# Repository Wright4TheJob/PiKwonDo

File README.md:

# PiKwonDo
A Raspberry Pi-based system for scoring TaeKwonDo sparring matches.

# Goals
The goal of this project is to create an inexpensive system for scoring TaeKwonDo sparring. This system is intended to be small and easily modified to suit the needs of individual Dojangs. The system is currently designed for electronic scoring manually triggered by corner judges.

Phase 1 of the judging system will use judge triggers connected by wires to the central controller. Phase 2 is intended to use wireless judge trigger systems or mobile phone connectivity.

While the system is designed to mimic expensive World TaeKwonDo-approved systems, it is not certified for official tournament use.

# Status
The project is under alpha development. Software has been developed but has yet to be tested with the hardware. Electronics are designed for single-sided PCB routing and have all completed initial design but have not been tested yet. Cases are designed for 3D printing. Hardware and software folders have individual README files with more particular statuses and todo items.

All design files and software are provided "as-is." Any stable releases will be bundled for easy download, but this does not guarantee suitability for your particular setup.

Bill of Materials (BOM) table validation: 

# Software
The judging software and UI is written in python and QT. A dedicated thread scans the status of judge controller buttons. Game logic and UI are run as the primary thread.
<!--Wireless versions of the software may use Twisted to create a local server.-->

# Electronics
Controllers use shift registers to store and sequentially read out the values of the buttons in each controller. Judge controllers have 10 buttons and the timer controller has 5. PCBs are designed for single-side milling, with traces no smaller than 0.4mm and trace gaps of 0.3mm. Through-hole components are used for hand soldering and occasional jumper wires are used.

# Hardware
The system is designed and tested on a Raspberry Pi 3B+. Physical wiring uses phone jacks and standard 4-conductor phone cables for data communication to judging triggers. Cases are designed for 3D printing and modeled in Solidworks.
<!--Future iterations may investigate the viability of using the Raspberry Pi Zero W.-->

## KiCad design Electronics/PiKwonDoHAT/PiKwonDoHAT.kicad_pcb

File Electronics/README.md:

# Electronics
The PiKwonDo is made of four different electrical boards bundled into three unique and connected elements: the processing core, the PiKwonDoHAT, the timer control board, and the judge control board.

All circuits and PCBs are modeled in KiCAD. PCBs are minimal complexity necessary. Boards are intended to be single-sided and capable of being milled on a home circuit board router.

# Processing Core
The core processing unit of the PiKwonDo is a Raspberry Pi. The system is being tested on a Raspberry Pi 3B+.

# PiKwonDoHAT
The PiKwonDoHAT board mounts to the Raspberry Pi and provides the GPIO interface to the RJ12 ports and external boxes. This board contains no logic, simply provides an I/O adapter.

# Peripheral Boxes
All the peripheral boxes (timer and judge boxes), use shift registers to store the button states and sequentially report buttons states to the processor when requested. This method reduces the number of data lines to the central processor and de-couples the number of data lines from the number of buttons per peripheral.

An LED is lighted by the shift pin of the shift register and will illuminate whenever the central processor is querying the state of the buttons.

## Timer
The timer control board contains 5 buttons: three to control the round timing (Start, Pause, Reset), and two penalty buttons (Red and Blue). A single shift register is used to output the state of these 5 buttons.

## Judge
The judge box board contains 10 buttons corresponding to point values of 1 through 5 for both red and blue. Two shift registers passing data in series are used to store the values of all 10 buttons.

# Status
Circuit diagrams have been completed and initial PCB layout and trace routing is done.

## TODO
* Finalize button positions on timer controller.
* Finalize BOM and component selection.
* Update component footprints to reflect BOM.
* Update trace size and spacing to ensure manufacturability.

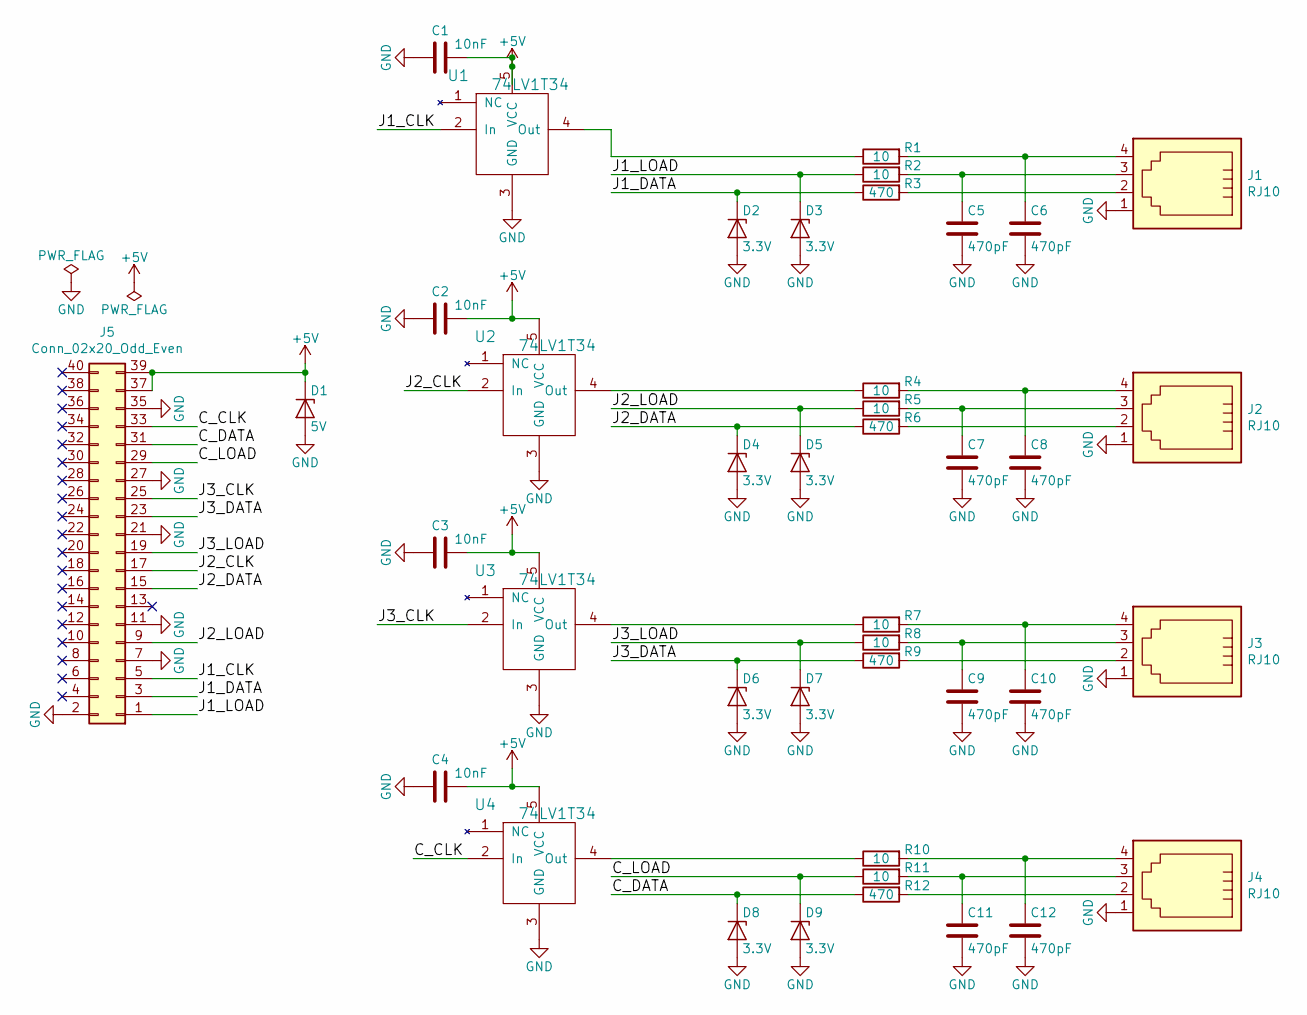
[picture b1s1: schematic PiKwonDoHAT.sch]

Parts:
C1, C2, C3, C4: 10nF; C_1206_3216Metric_Pad1.42x1.75mm_HandSolder
C5, C6, C7, C8, C9, C10, C11, C12: 470pF; C_1206_3216Metric_Pad1.42x1.75mm_HandSolder
D1: 5V; D_SOD-123
D2, D3, D4, D5, D6, D7, D8, D9: 3.3V; D_SOD-123
J1, J2, J3, J4: RJ10; RJ14
J5: Conn_02x20_Odd_Even; PinSocket_2x20_P2.54mm_Vertical
R1, R2, R4, R5, R7, R8, R10, R11: 10; R_1206_HandSoldering
R3, R6, R9, R12: 470; R_1206_HandSoldering
U1, U2, U3, U4: 74LV1T34; SOT-23-5_HandSoldering

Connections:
+5V: C1.1, C2.1, C3.1, C4.1, D1.1 (K), J5.37, J5.39, U1.5 (VCC), U2.5 (VCC), U3.5 (VCC), U4.5 (VCC)
/C_CLK: J5.33, U4.2 (In)
/C_DATA: D8.1 (K), J5.31, R12.1
/C_LOAD: D9.1 (K), J5.29, R11.1
/J1_CLK: J5.5, U1.2 (In)
/J1_DATA: D2.1 (K), J5.3, R3.1
/J1_LOAD: D3.1 (K), J5.1, R2.1
/J2_CLK: J5.17, U2.2 (In)
/J2_DATA: D4.1 (K), J5.15, R6.1
/J2_LOAD: D5.1 (K), J5.9, R5.1
/J3_CLK: J5.25, U3.2 (In)
/J3_DATA: D6.1 (K), J5.23, R9.1
/J3_LOAD: D7.1 (K), J5.19, R8.1
GND: C1.2, C2.2, C3.2, C4.2, C5.2, C6.2, C7.2, C8.2, C9.2, C10.2, C11.2, C12.2, D1.2 (A), D2.2 (A), D3.2 (A), D4.2 (A), D5.2 (A), D6.2 (A), D7.2 (A), D8.2 (A), D9.2 (A), J1.1, J2.1, J3.1, J4.1, J5.2, J5.7, J5.11, J5.21, J5.27, J5.35, U1.3 (GND), U2.3 (GND), U3.3 (GND), U4.3 (GND)
unnamed: C5.1, J1.3, R2.2
unnamed: C6.1, J1.4, R1.2
unnamed: C7.1, J2.3, R5.2
unnamed: C8.1, J2.4, R4.2
unnamed: C9.1, J3.3, R8.2
unnamed: C10.1, J3.4, R7.2
unnamed: C11.1, J4.3, R11.2
unnamed: C12.1, J4.4, R10.2
unnamed: J1.2, R3.2
unnamed: J2.2, R6.2
unnamed: J3.2, R9.2
unnamed: J4.2, R12.2
unnamed: R1.1, U1.4 (Out)
unnamed: R4.1, U2.4 (Out)
unnamed: R7.1, U3.4 (Out)
unnamed: R10.1, U4.4 (Out)

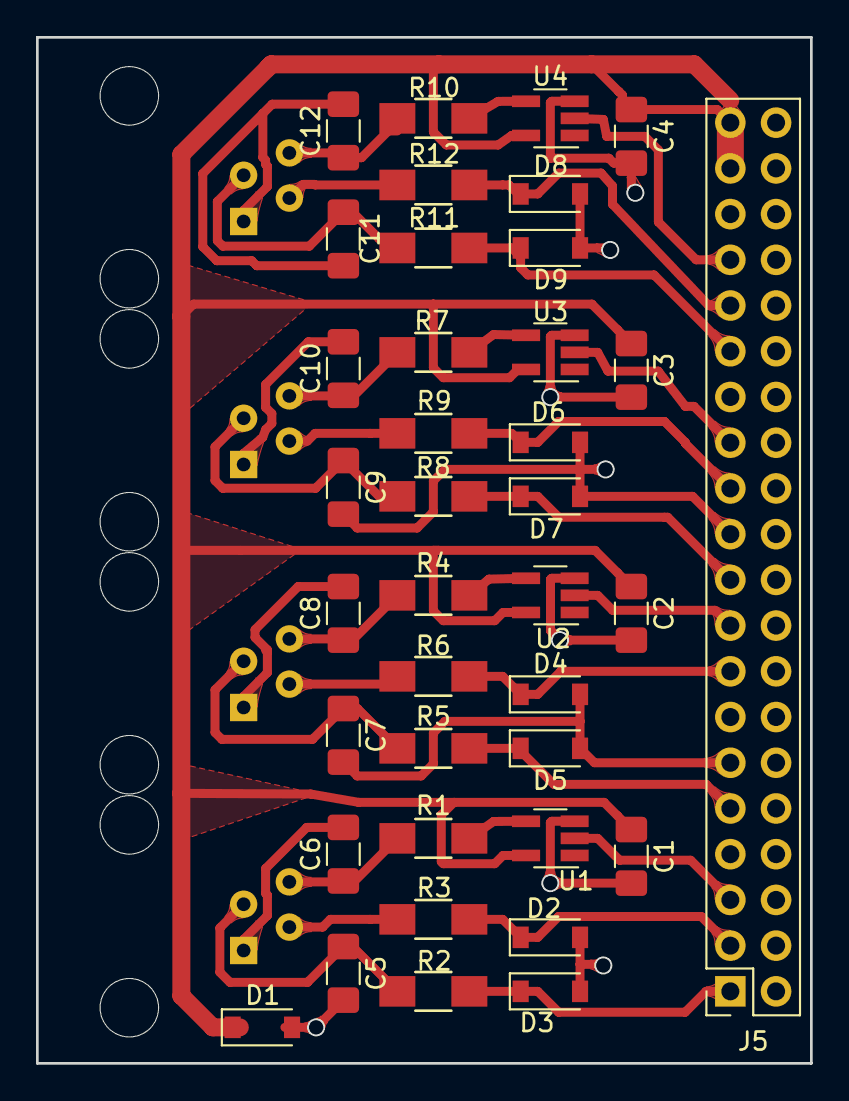
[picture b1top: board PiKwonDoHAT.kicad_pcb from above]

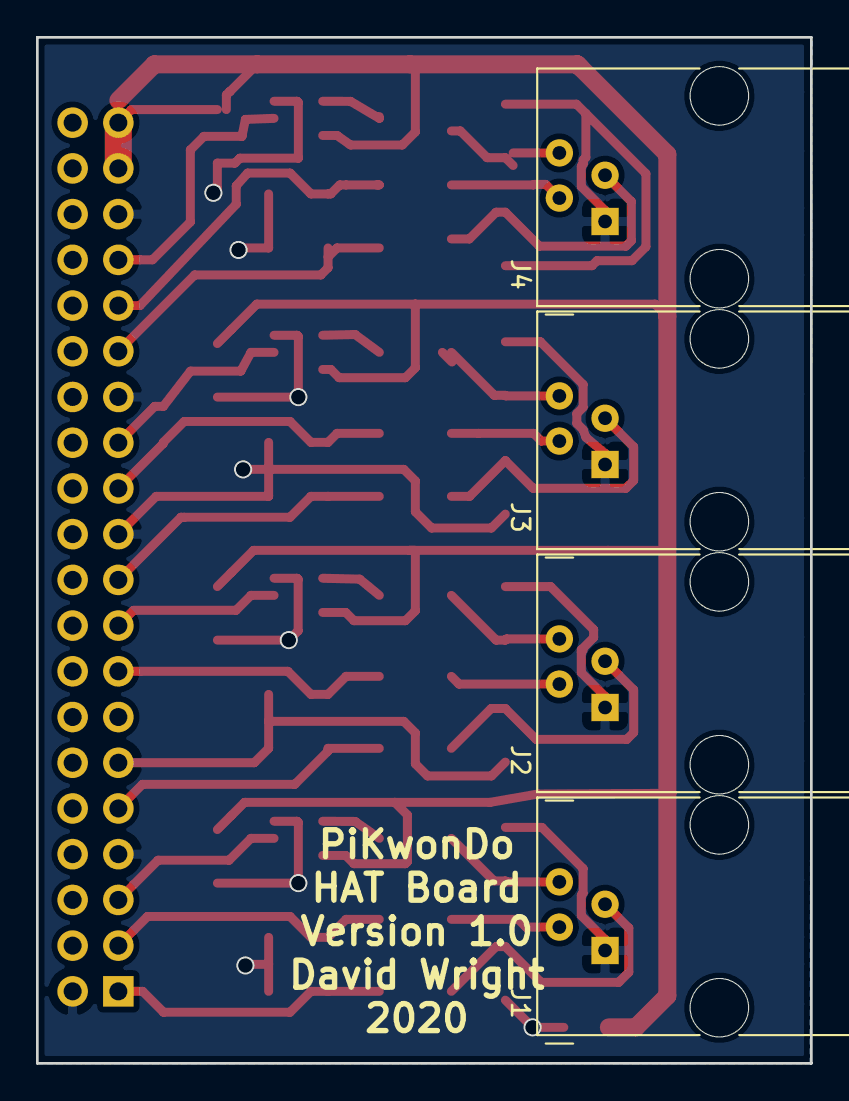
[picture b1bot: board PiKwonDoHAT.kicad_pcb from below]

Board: 2 copper layers, 43.0 x 57.0 mm, 42 parts (4 on the bottom side), 30 nets.

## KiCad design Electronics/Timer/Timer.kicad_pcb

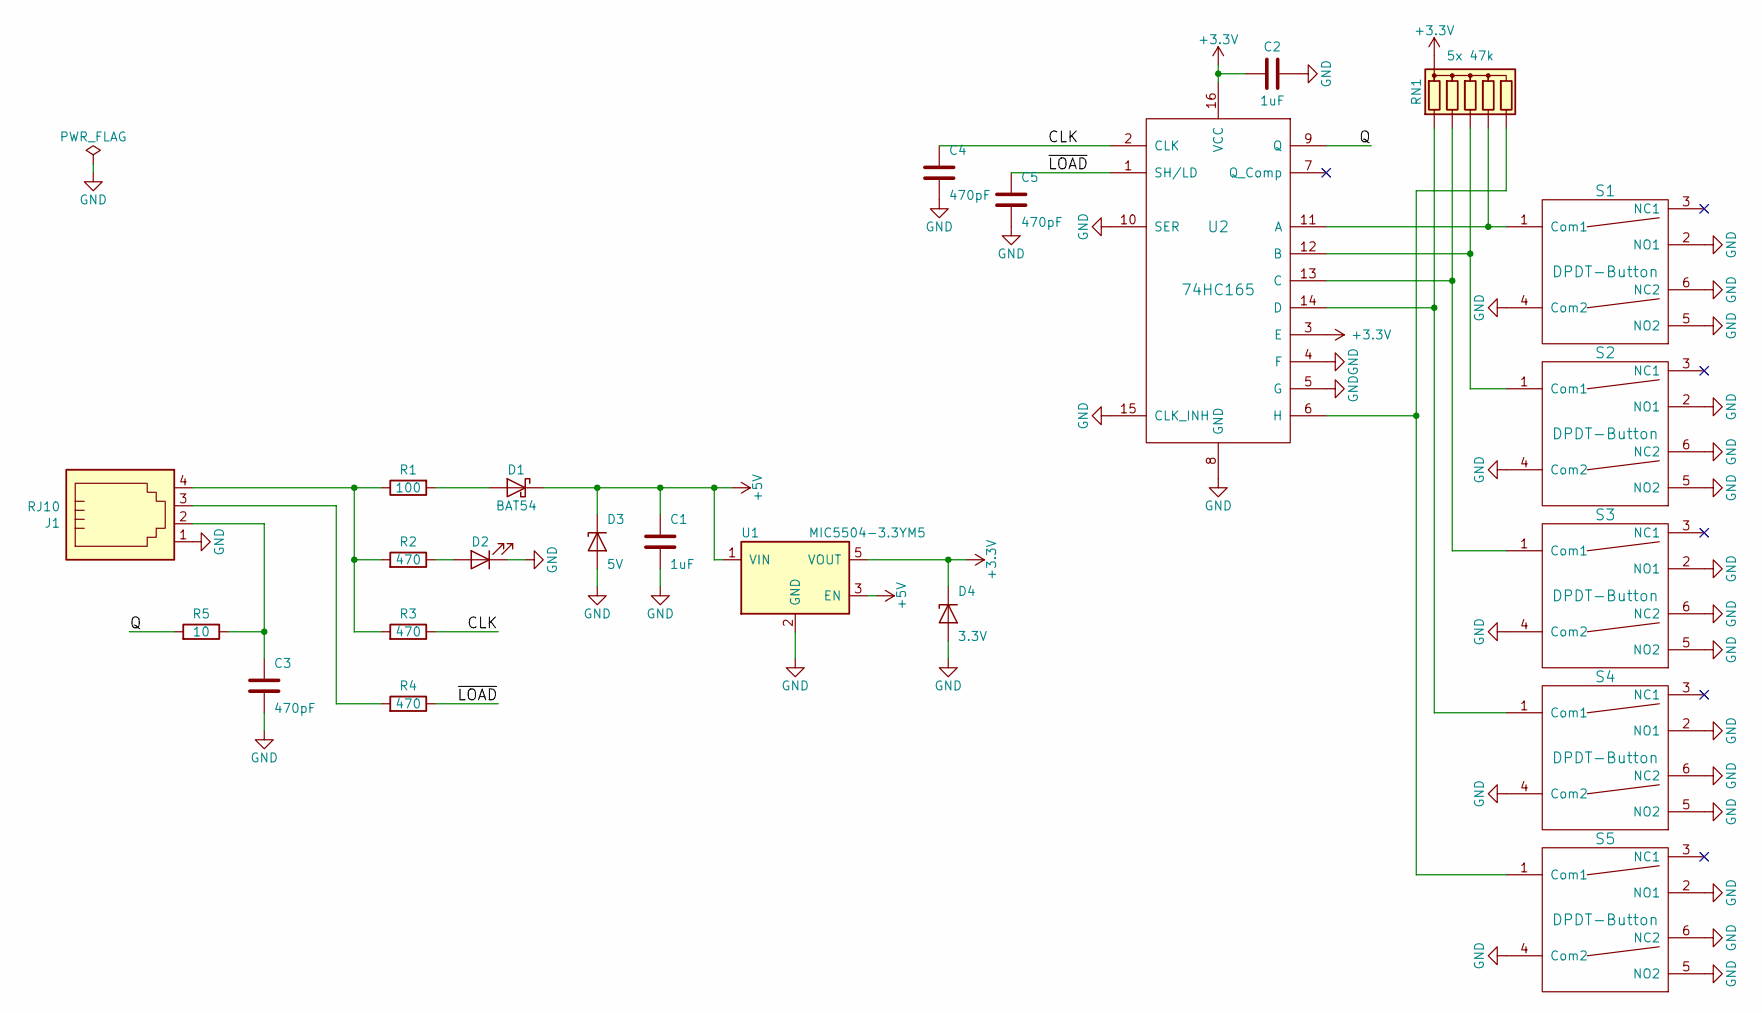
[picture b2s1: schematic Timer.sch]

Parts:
C1, C2: 1uF; C_1206_3216Metric_Pad1.42x1.75mm_HandSolder
C3, C4, C5: 470pF; C_1206_3216Metric_Pad1.42x1.75mm_HandSolder
D1: BAT54; D_SMA_Handsoldering
D2: LED; D_5W_P10.16mm_Horizontal
D3: 5V; D_SOD-323_HandSoldering
D4: 3.3V; D_SOD-123
J1: RJ10; RJ14
R1: 100; R_1206_HandSoldering
R2, R3, R4: 470; R_1206_HandSoldering
R5: 10; R_1206_HandSoldering
RN1: 5x 47k; R_Array_SIP6
S1, S2, S3, S4, S5: DPDT-Button; Switch-DPDT
U1: MIC5504-3.3YM5; SOT-23-5
U2: 74HC165; DIP-16_W7.62mm

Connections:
+3V3: C2.2, D4.1 (K), RN1.1 (common), U1.5 (VOUT), U2.3 (E), U2.16 (VCC)
+5V: C1.1, D1.1 (K), D3.1 (K), U1.1 (VIN), U1.3 (EN)
/CLK: C4.1, R3.1, U2.2 (CLK)
/Q: R5.2, U2.9 (Q)
/~LOAD~: C5.1, R4.1, U2.1 (SH/LD)
GND: C1.2, C2.1, C3.2, C4.2, C5.2, D2.1 (K), D3.2 (A), D4.2 (A), J1.1, S1.2 (NO1), S1.4 (Com2), S1.5 (NO2), S1.6 (NC2), S2.2 (NO1), S2.4 (Com2), S2.5 (NO2), S2.6 (NC2), S3.2 (NO1), S3.4 (Com2), S3.5 (NO2), S3.6 (NC2), S4.2 (NO1), S4.4 (Com2), S4.5 (NO2), S4.6 (NC2), S5.2 (NO1), S5.4 (Com2), S5.5 (NO2), S5.6 (NC2), U1.2 (GND), U2.4 (F), U2.5 (G), U2.8 (GND), U2.10 (SER), U2.15 (CLK_INH)
unnamed: C3.1, J1.2, R5.1
unnamed: D1.2 (A), R1.2
unnamed: D2.2 (A), R2.1
unnamed: J1.3, R4.2
unnamed: J1.4, R1.1, R2.2, R3.2
unnamed: RN1.2 (R1), S4.1 (Com1), U2.14 (D)
unnamed: RN1.3 (R2), S3.1 (Com1), U2.13 (C)
unnamed: RN1.4 (R3), S2.1 (Com1), U2.12 (B)
unnamed: RN1.5 (R4), S1.1 (Com1), U2.11 (A)
unnamed: RN1.6 (R5), S5.1 (Com1), U2.6 (H)

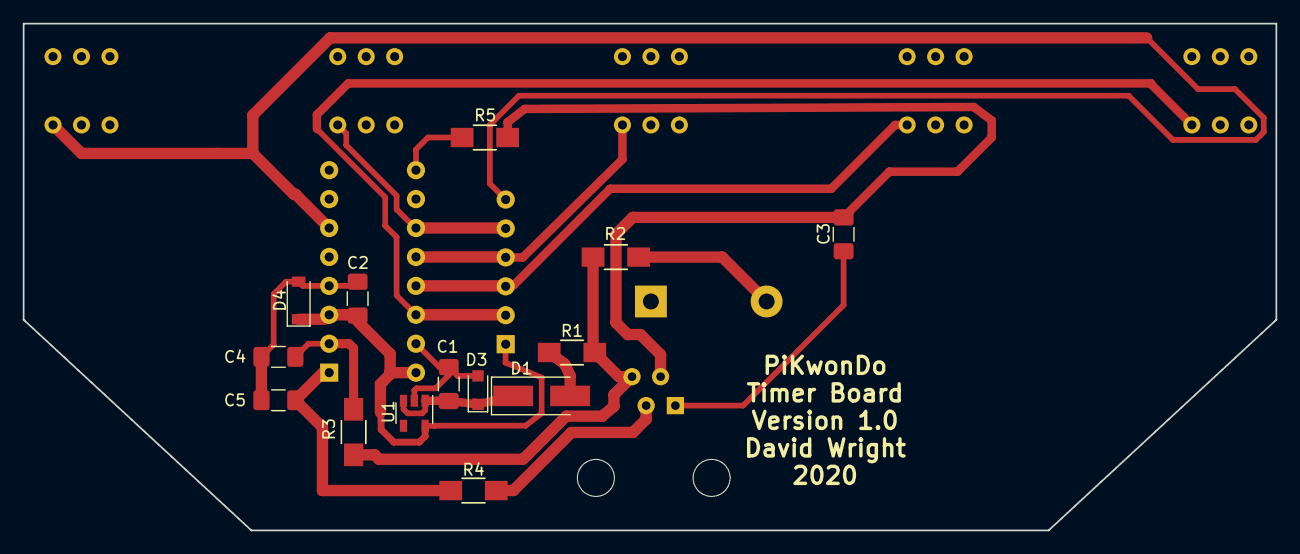
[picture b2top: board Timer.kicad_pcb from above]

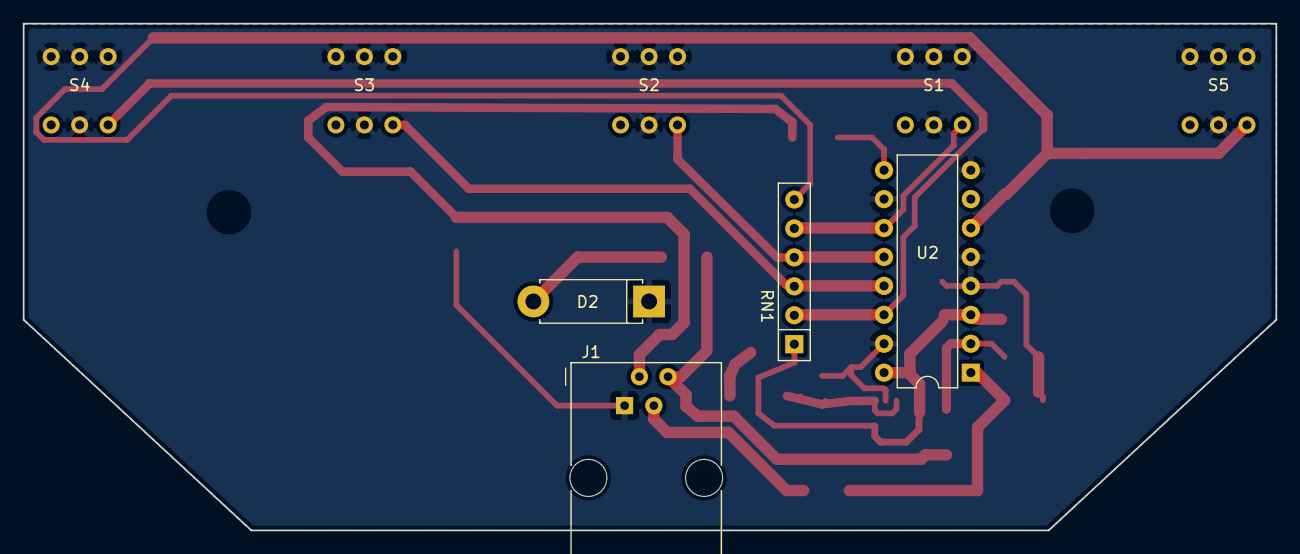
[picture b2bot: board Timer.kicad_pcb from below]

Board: 2 copper layers, 110.0 x 44.5 mm, 23 parts (9 on the bottom side), 16 nets.

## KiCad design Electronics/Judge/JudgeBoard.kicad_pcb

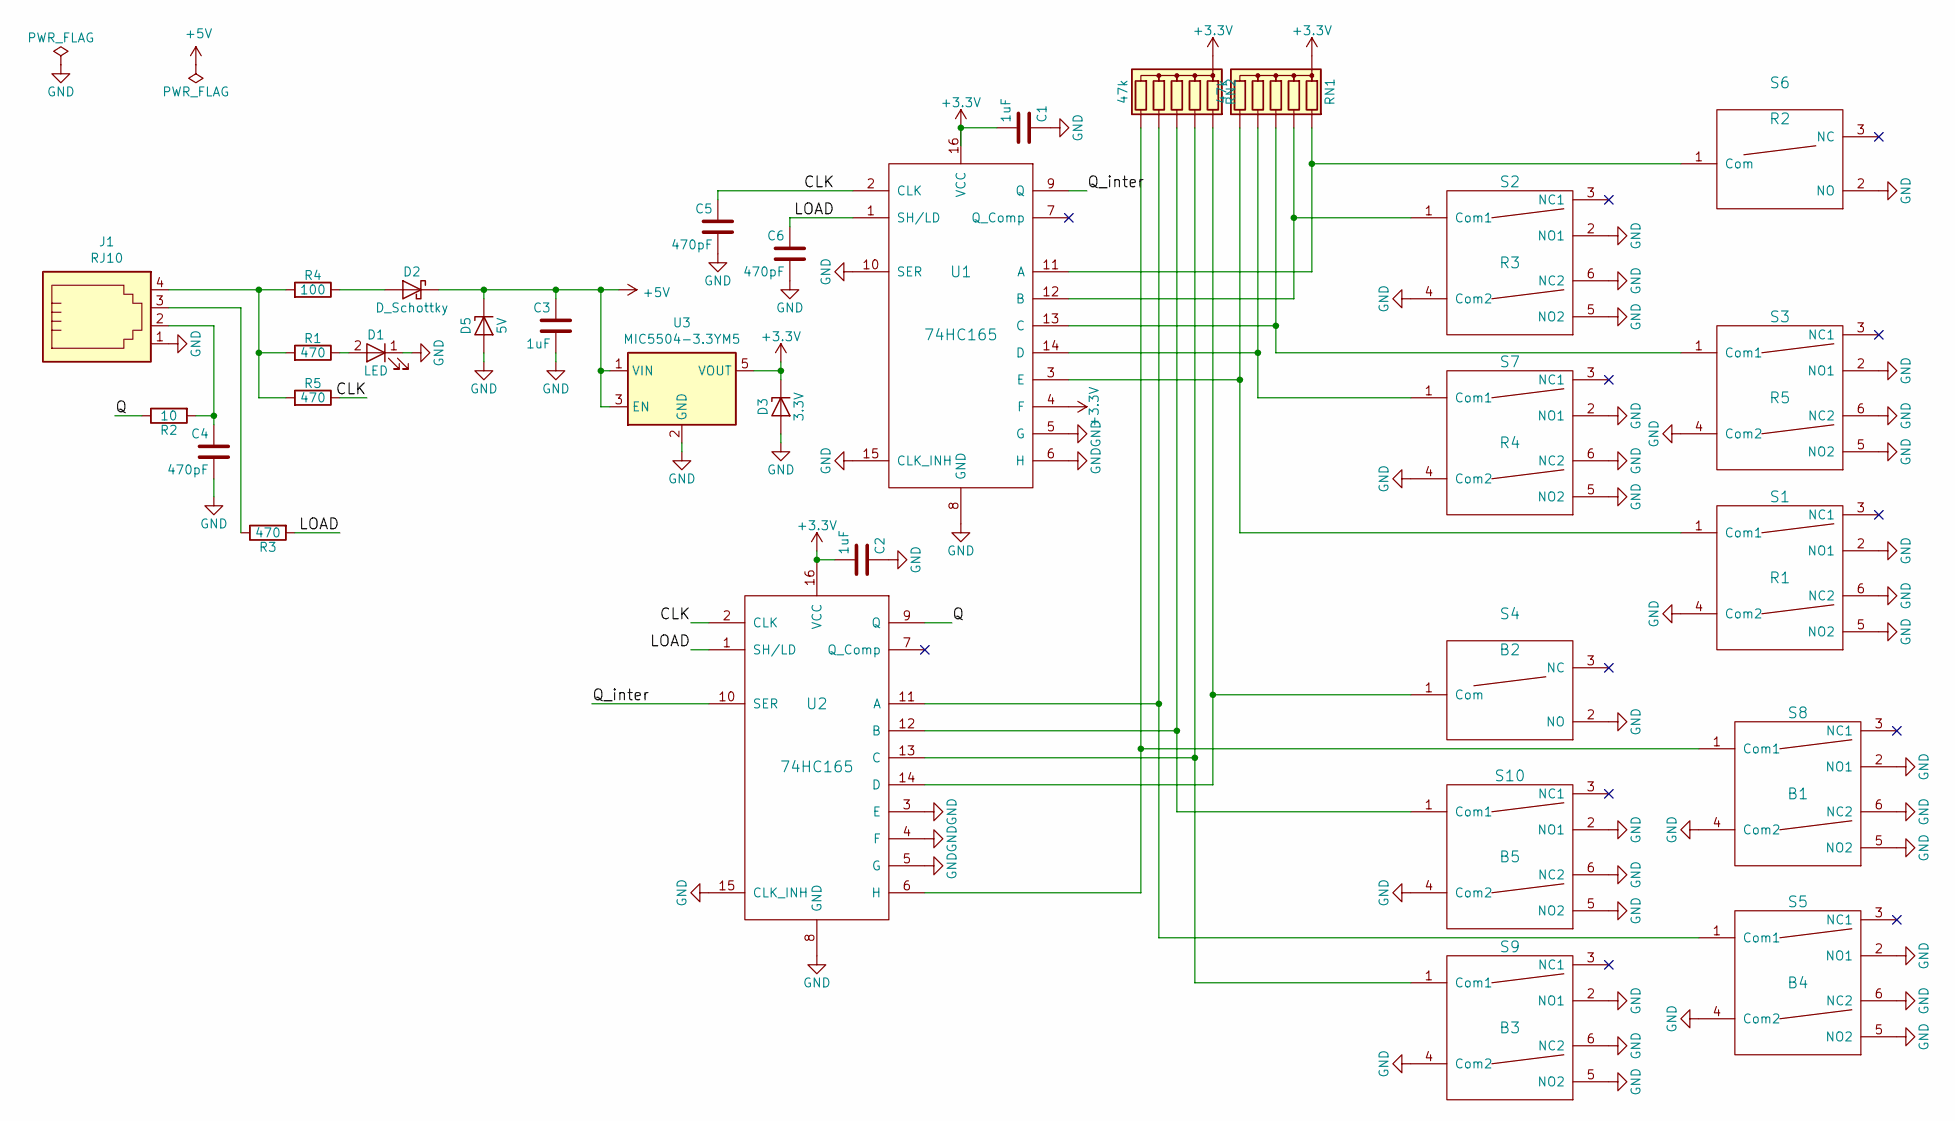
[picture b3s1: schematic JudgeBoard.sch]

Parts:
C1, C2, C3: 1uF; C_1206_3216Metric_Pad1.42x1.75mm_HandSolder
C4, C5, C6: 470pF; C_1206_3216Metric_Pad1.42x1.75mm_HandSolder
D1: LED; LED_D3.0mm_Spread
D2: D_Schottky; D_SMA_Handsoldering
D3: 3.3V; D_1206_3216Metric_Pad1.42x1.75mm_HandSolder
D5: 5V; SOD-80C
J1: RJ10; RJ14
R1, R3, R5: 470; R_1206_3216Metric_Pad1.42x1.75mm_HandSolder
R2: 10; R_1206_3216Metric_Pad1.42x1.75mm_HandSolder
R4: 100; R_1206_3216Metric_Pad1.42x1.75mm_HandSolder
RN1, RN2: 47k; R_Array_SIP6
S1: R1; MHPS2285V
S2: R3; MHPS2285V
S3: R5; MHPS2285V
S4: B2; Switch-SPDT
S5: B4; MHPS2285V
S6: R2; Switch-SPDT
S7: R4; MHPS2285V
S8: B1; MHPS2285V
S9: B3; MHPS2285V
S10: B5; MHPS2285V
U1, U2: 74HC165; DIP-16_W7.62mm_LongPads
U3: MIC5504-3.3YM5; SOT-23-5

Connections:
+3V3: C1.2, C2.2, D3.1 (K), RN1.1 (common), RN2.1 (common), U1.4 (F), U1.16 (VCC), U2.16 (VCC), U3.5 (VOUT)
+5V: C3.1, D2.1 (K), D5.1 (K), U3.1 (VIN), U3.3 (EN)
/CLK: C5.1, R5.1, U1.2 (CLK), U2.2 (CLK)
/LOAD: C6.1, R3.2, U1.1 (SH/LD), U2.1 (SH/LD)
/Q: R2.1, U2.9 (Q)
/Q_inter: U1.9 (Q), U2.10 (SER)
GND: C1.1, C2.1, C3.2, C4.2, C5.2, C6.2, D1.1 (K), D3.2 (A), D5.2 (A), J1.1, S1.2 (NO1), S1.4 (Com2), S1.5 (NO2), S1.6 (NC2), S2.2 (NO1), S2.4 (Com2), S2.5 (NO2), S2.6 (NC2), S3.2 (NO1), S3.4 (Com2), S3.5 (NO2), S3.6 (NC2), S4.2 (NO), S5.2 (NO1), S5.4 (Com2), S5.5 (NO2), S5.6 (NC2), S6.2 (NO), S7.2 (NO1), S7.4 (Com2), S7.5 (NO2), S7.6 (NC2), S8.2 (NO1), S8.4 (Com2), S8.5 (NO2), S8.6 (NC2), S9.2 (NO1), S9.4 (Com2), S9.5 (NO2), S9.6 (NC2), S10.2 (NO1), S10.4 (Com2), S10.5 (NO2), S10.6 (NC2), U1.5 (G), U1.6 (H), U1.8 (GND), U1.10 (SER), U1.15 (CLK_INH), U2.3 (E), U2.4 (F), U2.5 (G), U2.8 (GND), U2.15 (CLK_INH), U3.2 (GND)
unnamed: C4.1, J1.2, R2.2
unnamed: D1.2 (A), R1.1
unnamed: D2.2 (A), R4.1
unnamed: J1.3, R3.1
unnamed: J1.4, R1.2, R4.2, R5.2
unnamed: RN1.2 (R1), S6.1 (Com), U1.11 (A)
unnamed: RN1.3 (R2), S2.1 (Com1), U1.12 (B)
unnamed: RN1.4 (R3), S3.1 (Com1), U1.13 (C)
unnamed: RN1.5 (R4), S7.1 (Com1), U1.14 (D)
unnamed: RN1.6 (R5), S1.1 (Com1), U1.3 (E)
unnamed: RN2.2 (R1), S4.1 (Com), U2.14 (D)
unnamed: RN2.3 (R2), S9.1 (Com1), U2.13 (C)
unnamed: RN2.4 (R3), S10.1 (Com1), U2.12 (B)
unnamed: RN2.5 (R4), S5.1 (Com1), U2.11 (A)
unnamed: RN2.6 (R5), S8.1 (Com1), U2.6 (H)

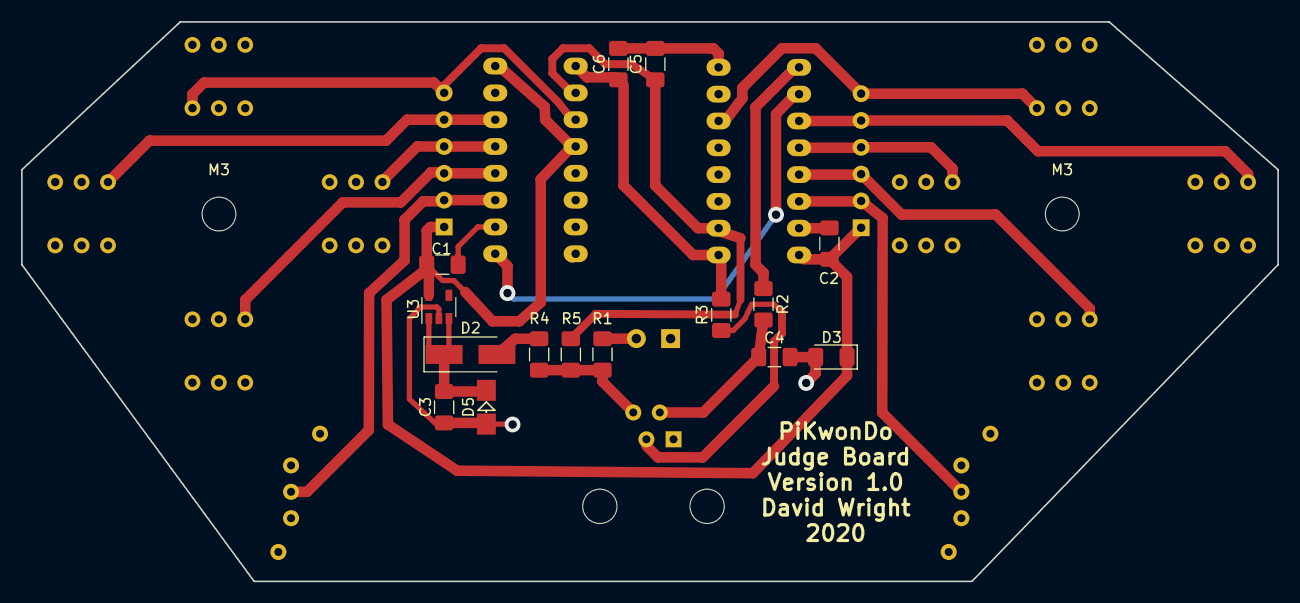
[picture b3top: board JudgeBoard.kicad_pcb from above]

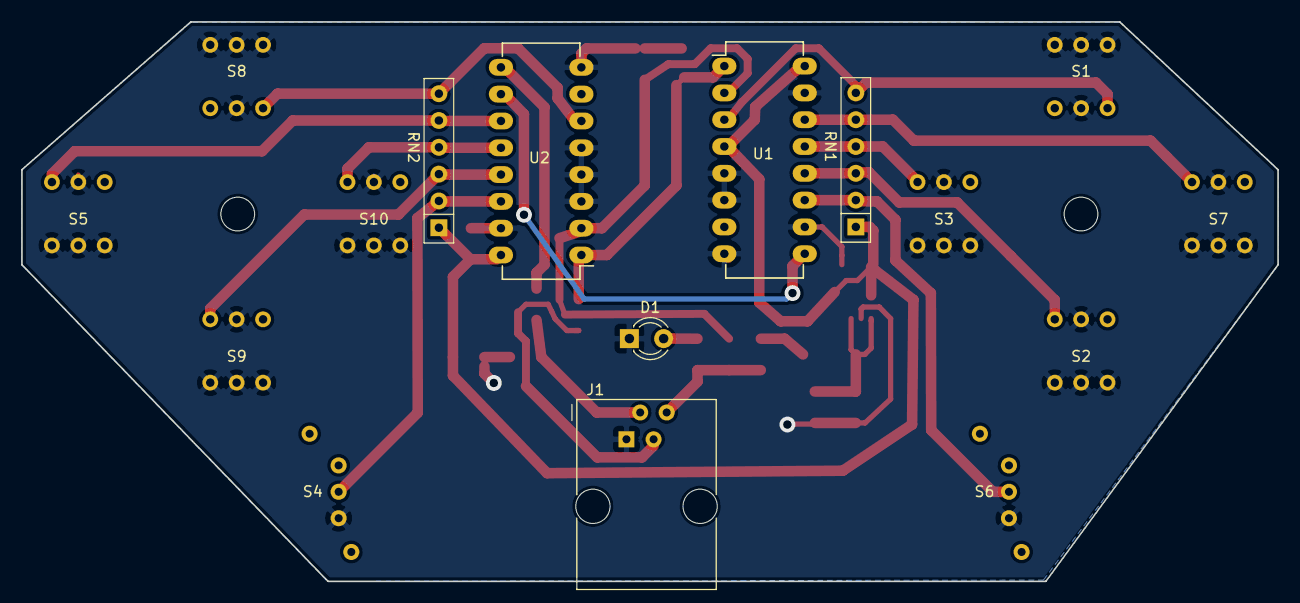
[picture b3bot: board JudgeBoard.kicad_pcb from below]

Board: 2 copper layers, 119.0 x 53.0 mm, 33 parts (16 on the bottom side), 22 nets.

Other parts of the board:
M3, M3#2: MountingHole_3.2mm_M3

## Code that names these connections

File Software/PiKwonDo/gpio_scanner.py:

#! /bin/env/python3
# David Wright
# Copyright 2017
# Written for Python 3.5.6
"""Scan hardware status for buttons and emit correct signal."""
import os
import time
import threading
try:
    import RPi.GPIO as GPIO
except ImportError:
    print("Not running on Pi")


class ButtonHandler(threading.Thread):
    """Detect desired signal from GPIO pin and emits signal after debounce."""

    def __init__(self, pin, func, edge='both'):
        """Initialize timing thread and input assignments."""
        super().__init__(daemon=True)

        self.edge = edge
        self.func = func
        self.pin = pin
        self.glitchtime = 0.00005  # 50 us
        self.lastpinval = GPIO.input(self.pin)
        self.glitch_lock = threading.Lock()
        if self.edge == 'rising':
            gpio_edge = GPIO.RISING
        elif self.edge == 'falling':
            gpio_edge = GPIO.FALLING

        GPIO.add_event_detect(pin, gpio_edge, callback=self)

    def __call__(self, *args):
        """Lock thread and start new timer."""
        if not self.glitch_lock.acquire(blocking=False):
            return

        glitch_timer = threading.Timer(
            self.glitchtime, self.glitch_done, args=args)
        glitch_timer.start()

    def glitch_done(self, *args):
        """Emit assigned signal when valid signal detected."""
        pinval = GPIO.input(self.pin)
        rising = (pinval == 0 and self.lastpinval == 1)
        falling = (pinval == 1 and self.lastpinval == 0)
        if ((rising and (self.edge in ['falling', 'both'])) or
                (falling and (self.edge in ['rising', 'both']))):
            self.func(*args)

        self.lastpinval = pinval
        self.glitch_lock.release()


class PeriodicActionThread(threading.Thread):
    """Perform an action on a regular repeating schedule."""

    def __init__(self, function, period):
        """Start thread and setup settings."""
        super().__init__()
        self.function = function
        self.lock = threading.Lock()
        self.period = period/1000
        self.step()

    def step(self):
        """Perform desired action in thread-safe way."""
        if self.lock.acquire(blocking=False):
            self.function()
            self.lock.release()
        self.timer = threading.Timer(self.period, self.step)
        self.timer.start()


class HardwareConfiguration():
    """Configure pins for each generation of hardware."""

    def __init__(self):
        """Set class variables."""
        self.load_pins = False
        self.clock_pins = False
        self.data_pins = False
        # cluster clock, step, and data pins
        self.set_pinout()
        self.setup_gpio()

    def set_pinout(self):
        """Assign pins to circuit expectations."""
        j0_clk_pin = 2
        j0_load_pin = 3
        j0_dat_pin = 4

        j1_clk_pin = 17
        j1_load_pin = 27
        j1_dat_pin = 22

        j2_clk_pin = 10
        j2_load_pin = 9
        j2_dat_pin = 11

        # timer
        t_load_pin = 19
        t_clk_pin = 6
        t_dat_pin = 26

        self.load_pins = [j0_load_pin, j1_load_pin, j2_load_pin, t_load_pin]
        self.clock_pins = [j0_clk_pin, j1_clk_pin, j2_clk_pin, t_clk_pin]
        self.data_pins = [j0_dat_pin, j1_dat_pin, j2_dat_pin, t_dat_pin]

    def setup_gpio(self):
        """Set GPIO pin numbering scheme and pin initialization."""
        GPIO.setmode(GPIO.BCM)
        GPIO.setwarnings(False)
        initialize_pins(self.load_pins)
        initialize_pins(self.clock_pins)
        initialize_pins(self.data_pins)


class HardwareControllerScanner():
    """Monitor hardware status by regular sweep scans."""

    try:
        import RPi.GPIO as GPIO
    except ImportError:
        print("Not running on raspberry Pi.")

    def __init__(self):
        """Set initial pin numbers and class values."""
        name = os.uname()
        self.running_raspi = name[1] == "raspberrypi"

        self.target_queue = None
        # last meaningful bit in the judge controller is the 13th
        self.bits_to_scan = 10
        self.scan_period = 5  # ms
        if self.running_raspi:
            self.pinout = HardwareConfiguration()
        self.pin_change_signal_array = None

        self.old_bits = False

        _ = PeriodicActionThread(self.step, self.scan_period)

    @property
    def pin_change_signals(self):
        """Return array of button_signal-signal matrix."""
        return self.pin_change_signal_array

    def read_bits(self):
        """Read one bit from each data input pin."""
        result = [GPIO.input(pin) for pin in self.pinout.data_pins]
        return result

    def load_data(self):
        """Load data into shift registers."""
        for pin in self.pinout.load_pins:
            pulse_gpio_pin_high(pin)

    def shift_data(self):
        """Cycle the clock pin on each controller."""
        for pin in self.pinout.clock_pins:
            pulse_gpio_pin_low(pin)

    def scan_bits(self):
        """Read all data from controllers."""
        result = []
        # send load signal
        self.load_data()
        # Read bits from all controllers
        for _ in range(0, self.bits_to_scan):
            milliseconds(0.1)  # Wait for signals to stabilize
            result.append(self.read_bits())
            # Read a single bit from each of controllers
            self.shift_data()
        return result

    def step(self):
        """Cycle bit scanning and detects changes."""
        if self.running_raspi is True:
            new_bits = self.scan_bits()
        if self.old_bits and self.running_raspi:
            changes = compare_bits(self.old_bits, new_bits)
            changed = is_nonzero(changes)
            if changed:
                print(new_bits)
                # time = -1
                # if self.target_queue is not None:
                # self.target_queue.put(newBits)
                # self.bit_changed.emit(time,changes)
        self.old_bits = new_bits

    def __del__(self):
        """Cleanup GPIO settings on close."""
        GPIO.cleanup()  # Clean up


class BitDecoder():
    """Correlate button press events to signals to emit."""

    def __init__(self, pikwondo):
        """Create matrix to lookup correct signal to emit."""
        self.main_process = pikwondo
        bits = 13
        controllers = 4
        for _ in range(0, bits):
            for _ in range(0, controllers):
                pass
        # [pin1,pin2,pin3...]
        # [bit1,bit1,bit1...]
        # [bit2,bit2,bit2...]
        # [bit3,bit3,bit3...]
        # where each element is a touple of rising and falling signals
        # or rising is 1, falling is -1, and
        self.pin_change_signal_array = [[1, 0, -1], [0, 0, 0]]

        # connect(lambda: self.main_process.redPoint(1))

    @property
    def pin_signal_array(self):
        """Return pin change signal array, or calculate it."""
        return self.pin_change_signal_array

    def __del__(self):
        """Cleanup gpio pin statuses on close."""
        # GPIO.cleanup() # Clean up
        # self.wait()


def initialize_pins(pins, pin_type='output'):
    """Set pinmode for list of GPIO pin numbers."""
    for pin in pins:
        if pin_type == 'output':
            GPIO.setup(pin, GPIO.OUT)
        elif pin_type == 'input':
            GPIO.setup(pin, GPIO.IN)


def pulse_gpio_pin_high(pin):
    """Set a gpio pin high then low, with appropriate delay."""
    GPIO.output(pin, GPIO.HIGH)
    milliseconds(0.2)
    GPIO.output(pin, GPIO.LOW)


def pulse_gpio_pin_low(pin):
    """Set a gpio pin low then high, with appropriate delay."""
    GPIO.output(pin, GPIO.LOW)
    milliseconds(0.2)
    GPIO.output(pin, GPIO.HIGH)


def milliseconds(duration):
    """Delay for desired number of milliseconds."""
    time.sleep(0.001*duration)


def compare_bits(olds, news):
    """Subtract 2D list to determine changes to bit state."""
    rows = len(olds)
    cols = len(olds[0])
    delta = [[0] * cols for i in range(rows)]
    for i in range(0, rows):
        for j in range(0, cols):
            delta[i][j] = news[i][j] - olds[i][j]
    return delta


def is_nonzero(delta):
    """Return True if any element of 2D list is nonzero."""
    nonzero = False
    for row in delta:
        for element in row:
            if element != 0:
                nonzero = True
    return nonzero

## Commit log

2018-03-19 Wrote initial requirements, added WT rules.
2018-03-19 Updated README to include goals, status, software, and hardware.
2018-03-19 Added skeleton python program.
2018-03-19 Added fullscreen and color backgrounds.
2018-03-21 Created block diagram, updated requirements
2018-03-22 First UI using primative painting methods.
2018-03-22 Refactored for simpler class structure, added core actions and menu.
2018-03-23 Window resizing, menu-based scoring and penalties.
2018-03-23 Working timer added.
2018-03-23 Moved multithreading to QThread.
2018-03-23 Added round timer lockouts.
2018-03-23 Auto-trigger sequence of rounds and breaks.
2018-03-23 Initial BOM added
2018-03-27 Added GPIO listener thread.
2018-03-30 Fixed bug in current time function. Added disqualification check.
2018-04-04 Updated BOM
2018-04-05 Added Raspberry Pi components to BOM
2018-04-05 Added installation command for PyQt5 on Pi
2018-04-11 Added Raspberry Pi source, updated switch model
2018-04-15 Initial models.
    Modeled proto board and push button.
2018-04-19 Updated Judge Case
    Added DIP Socket, RJ12 Socket, Case Bottom. Positioned top buttons.
2018-04-20 Main Case, Trigger Button
2018-04-20 Added initial falling edge function triggering and judge logic
2018-04-21 Initial Main Box completed
2018-04-22 Created Timer Case
    Laid out timer board components without LEDs, created both case sides.
2018-04-22 Restructured File System
2018-04-22 Initial Judge Case model
2018-04-23 Refactored Main Box, added STLs.
2018-04-25 Main Box model tweaks
    Fixed a collision in Main Box Center, updated interferance fit tolerances and text.
2018-04-25 Updated Timer Box, exported STLs.
2018-04-25 Updated Judge Box
    Moved components and avoided collisions.
2018-04-25 Exported STLs, updated cover fits in JudgeCover
2018-04-26 Updated taper on button sockets
2018-04-26 Updated Trigger Button interferance fit
2018-04-26 Updated Trigger Cover fit
2018-04-26 Updated trigger button throw distance.
2018-04-27 Updated Main Box Case Center
    Allowed screws to be any length, modified clearances.
2018-04-27 Updated GPIO code
2018-04-27 Imported GPIO library
2018-04-27 Updated board mode
2018-04-27 Moved text order
2018-04-27 Corrected method callback in GPIO Listener
2018-04-27 Updated error in penalty method call
2018-04-27 Updated arguments for GPIO functions
2018-04-27 UPdated GPIORead function to self.gpioRead
2018-04-27 Made pin assignments class level rather than local
2018-04-27 Added debounce class
2018-04-27 Corrected spelling
2018-04-27 Logic bug fixes
2018-04-27 Added debug prints
2018-04-27 Updated debounce class
2018-04-27 Convereted tabs to spaces
2018-04-28 Updated Top Button Tab Thickness.
2018-04-28 Simplified and implemented judge trigger system logic.
2018-04-28 Shorted debounce time and removed dual deounce.
2018-04-28 Simplified debouncing and tracking of judge pins
2018-04-28 Corrected self. error
2018-05-04 Added new controller design options
2018-05-04 Added unit test file
2018-05-04 Initial shift-register based judge controller schematic
2018-05-10 Updated symbols and footprints for pushbutton
2018-05-14 Added README for electronics.
2018-05-14 Updated button layout ideas.
2018-05-14 UPdated judge board layout
2018-06-07 Controller design iteration, code refactoring modifications
2018-06-07 Began refactoring GUI to separate file. Ignored gcode files.
2018-06-07 Corrected gitingore for gcode files.
2018-06-13 Debugged initialization behavior. Isolated GPIO.
2018-06-13 Updated fulscreen view.
2018-06-16 Restuctured GPIO listener.
2018-06-17 Updated judge controller case.
2018-06-18 Added libraries with customized components.
2018-06-19 Simplified judge controller schematic and pcb
2018-06-19 Added point values to button covers.
2018-06-19 Updatd button and judge box assembly.
2018-06-19 Updated trace locations
2018-06-20 Reduced judge board to 2 jumpers
2018-06-20 Cleaned up judge controller PCB, removed 3 jumpers
2018-06-20 Finished HAT schematic
2018-06-21 Created HAT schematic and PCB
2018-06-24 Finalized HAT PCB design
2018-06-24 Updated status in README for each folder.
2018-06-24 Updated trace routing on timer circuit
2018-06-24 Updated FlatCAM project for timer board
2018-06-26 Updated BOM and component selection
2018-06-29 Updated Judge Board model and case.
2018-06-30 Significant updates to Judge Controller Case.
2018-07-01 Judge controller 3D printed parts finalized.
2018-07-01 Reorganized file structure for case model.
2018-07-01 Initial timer case assembly complete.
2018-07-01 Updated timer case text.
2018-07-09 Added circuit protection elements to judge controller schematic
2018-07-09 Finalized component selection for Judge Controller
2018-07-10 Updated footprints
2018-07-12 Updated components list
2018-07-12 Updated Judge PCB layout to include new footprints
2018-07-12 Updated Timer schematic and updated PCB footprints
2018-07-13 Updated circuit protection elements to HAT schematic board.
2018-07-15 Updated parts lits
2018-07-15 Updated timer and judge case hardware.
2018-07-16 Updated Timer PCB and exported GERBERS
2018-07-18 Updated CAM files for Timer and PCB for HAT
2018-07-18 Finalized HAT PCB
2018-07-22 Updated BOM and CAM files for HAT PCB
2018-07-22 Removed extra files
2018-07-23 Updated Judge PCB routing
2018-07-24 Testing dimensions for top buttons.
2018-07-25 Simplified Judge PCB and button design.
2018-07-26 Updated Timer Box case.
2018-07-27 Added voltage buffer to HAT schematic
2018-07-27 Completed HAT PCB
2018-07-28 Updated HAT PCB footprints and BOM
2018-07-28 Tweaked and cleaned up hat schematic:
    * Made all input resistors 470 ohms
    * Cleaned up graphically
    * Reassigned reference numbers
2018-07-28 Tweaked schematic a bit further; changed PCB references to match schematic.
2018-07-28 Synchronized PCB with schematic netlist.
2018-07-28 Tweaked bypass capacitor layouts.
2018-07-28 Removed temporary files from hat directory.
2018-07-29 Updated Timer schematic, footprints, BOM, and PCB
2018-07-29 Changed diode footprints to SOD-323 (Hand)
2018-07-29 Updated gitignore to include Kicad temp files.
2018-07-29 Added MIC5504 and SN74LV1t34 datasheets.
2018-07-29 Revert "Merge branch 'master' into electronics-tweaks; overwrite 'master' hat changes"
    This reverts commit 8490e2c3782f3b2eaf596155d8884dc6cd65858c, reversing
    changes made to 143268d8e254d2edd056497eb53e137ee58f0f7c.
2018-07-29 Cleaned up timer directory
2018-07-29 Timer: Restore David's updated schematic and PCB from earlier failed merge.
2018-07-29 Timer: Cleaned up schematic; reassigned reference numbers.
2018-07-29 Synchronized PCB with new netlist; cleaned up glitches.
2018-07-29 Timer: Rerouted to eliminate jumpers, at the cost of a few 1206's with two traces underneath.
2018-07-29 Timer: Increased C2 to 1 uF (per datasheet for U1 stability); brought RN1 back to 3.3 V instead of 5 V.
2018-08-22 Updated columns in BOM to allow copy and paste for mouser
2018-08-22 Updated Timer project to kicad 5
2018-08-23 Initial HAT manufacturing file preparation
2018-08-25 Updated HAT manufacturing files
2018-08-31 Updated gitignore to transfer gcode files
2018-08-31 Added electronics manufacturing files
2018-09-04 Updated Timer Manufacturing files
2018-09-04 Updated timer trace for proper clearance
2018-09-13 Updated Timer PCB and manufacturing files
2018-09-13 Mirrored PCB across x axis for gcode generation
2018-09-13 Added Flatcam project for Timer Board
2018-09-15 Updated Judge PCB for manufacturability
2018-09-15 Updated software README to add launch instructions and TODO
2018-09-16 Updated Timer PCB for manufacturability
2018-09-16 Updated HAT PCB slightly
2018-09-16 Converted whitespace to spaces
2018-09-17 Updated mill tool diameter
2018-10-02 Resave without major changes
2018-10-10 Corrected HAT board diode selection
2018-10-10 Reconnected schematic symbols
2018-10-10 Trace widening for manufacturing and assembly ese
2018-10-12 Updated HAT trace widths
2018-10-12 Corrected component list for Timer board
2018-10-12 Updated trace widths
2018-10-14 Updated manufacturing files
2018-10-16 Updated HAT BOM.
2018-10-16 Cleanup old functions.
2018-10-16 Added software gitignore.
2018-10-16 Updated library footprint references
2018-10-17 Updated class diagram
2018-10-17 Removed unnecessary class diagram file
2018-10-17 Added unit testing script using coverage.
2018-10-18 Created initial Utilities file for helper classes.
2018-10-18 First functional tests.
2018-10-18 Added drop box which emits QT signal.
2018-10-20 Refactored to remove QT from main file
2018-10-20 Updated test to not launch GUI for each test
2018-10-20 Removed QT from timer, implemented tests.
2018-10-20 Removed unused python file.
2018-10-20 Added two timer tests.
2018-10-20 Listed initial events for logging.
2018-10-20 Updated classes to include timer object.
2018-10-20 Excluded python coverage reports.
2018-10-22 Updated links and footprints for larger components.
2018-10-22 Updated zener diode footprint and layout
2018-10-22 Minor updates as refactoring happens
2018-10-23 Minor trace cleanup
2018-10-23 Updating judge circuits and pcb to match timer
2018-10-25 Removed extra lines in BOM
2018-10-25 Added goodtables badge to README
2018-11-14 Added documentation files
2018-11-14 Moved docs to root
2018-11-14 Updated index
2018-11-14 Moved files
2018-11-14 Added build folder
2018-11-14 Updated README with link to docs
2018-11-14 Updated docs to sphinx_rtd_theme
2018-11-14 Minor update to gitignore
2018-11-15 TimerTest script now compiles and runs.
2018-11-18 Modifications for queue implementation.
2018-11-26 Updated GPIO test program
2018-11-27 Updated Main Box Solidworks
2018-11-28 Minor update to allow building.
2018-11-28 Initial commit.
2018-11-28 Updated author
2018-11-28 Switched to tested in python 3.6
2018-11-28 Added pyqt5.
2018-11-28 Added travisci badge.
2018-11-28 Updated to commit coverage.
2018-11-28 Updated coveragerc
2018-11-28 File updates
2018-11-28 Updated data validation badges.
2018-12-02 Updated TimerTest to run in 3.5.6
2018-12-02 Added print of data
2018-12-02 Updated os name
2018-12-02 Removed RPi dummy module
2018-12-02 Addedd GPIO.setmode()
2018-12-03 Updated PCB and Timer cases.
2018-12-03 Updated Timer PCB mount holes
2018-12-03 Updated for PEP8 compliance.
2018-12-04 Updated style for PEP8.
2018-12-04 Updated tests for correct initialization.
2018-12-04 Corrected filepaths.
2018-12-04 PiKwonDo
2018-12-04 Rename GUI.py to gui.py
2018-12-05 Tested on-device and reading values
2018-12-05 Updated name and standard to PEP8.
2018-12-05 Cleaup gpio_scanner style.
2018-12-06 Updated documents.
2018-12-06 Included link to Github.io page.
2018-12-06 Minor changes.
2018-12-06 Renamed gpio scanner.
2018-12-06 Updated to resolve bad merge.
2018-12-06 UPdated.
2018-12-06 Brought back good changes to files.
2018-12-06 Refactored for PEP8 compliance.
2018-12-06 Updated style and workflow.
2018-12-06 Corrected unit_test filepath.
2018-12-06 Another filepath correction.
2018-12-06 Rename Utilities.py to utilities.py
2018-12-14 Hold the shift pin high between pulses and pulse low.
2019-01-15 Corrected design error in Timer board, updated routing.
2019-01-15 Updated trace routing and RJ12 footprint.
2019-01-17 Intermediate commit while moving components to final locations.
2019-01-17 Finalized trace routing and part placement.
2019-01-19 Updated trace routing and board outline. Added mounting holes.
2019-01-22 Initial flat model in Freecad.
2019-03-01 Minor format and docstring mods
2019-03-01 Partial updates to PiZero integration.
2019-03-01 Updated to mate with RasPi Zero, reduced footprint significantly.
2020-01-23 Updated boards for two-sided manufacture.
2020-04-13 Added STEP files for hat
2020-04-13 Finalized STEP files
2020-05-05 Push misc solidworks updates
2020-06-07 Added grips to judge case bottom.
2020-06-07 Created bom and updated pcb
2020-06-10 Increased size of grips
2020-07-18 Updated diode footprint for improved solderability
2020-07-26 Updated controller designs.
2020-08-01 Updated component sourcing
2020-08-09 Included recycling symbols.
2025-10-20 Added renders of controller.
